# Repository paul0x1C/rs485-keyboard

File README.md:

# RS-485 Keyboard PCB
The PCB is equipped with an Arduino Nano and 24 keyboard switches and communicates via RS-485.
The keys are arranged in a 8x3 matrix. It's also possible to connect a rotary encoder and potentiometer. The keyboard is meant to control leds: press R and scroll the rotary encoder to alter the red value or H to alter hue, but I didn't code that yet.
# pictures

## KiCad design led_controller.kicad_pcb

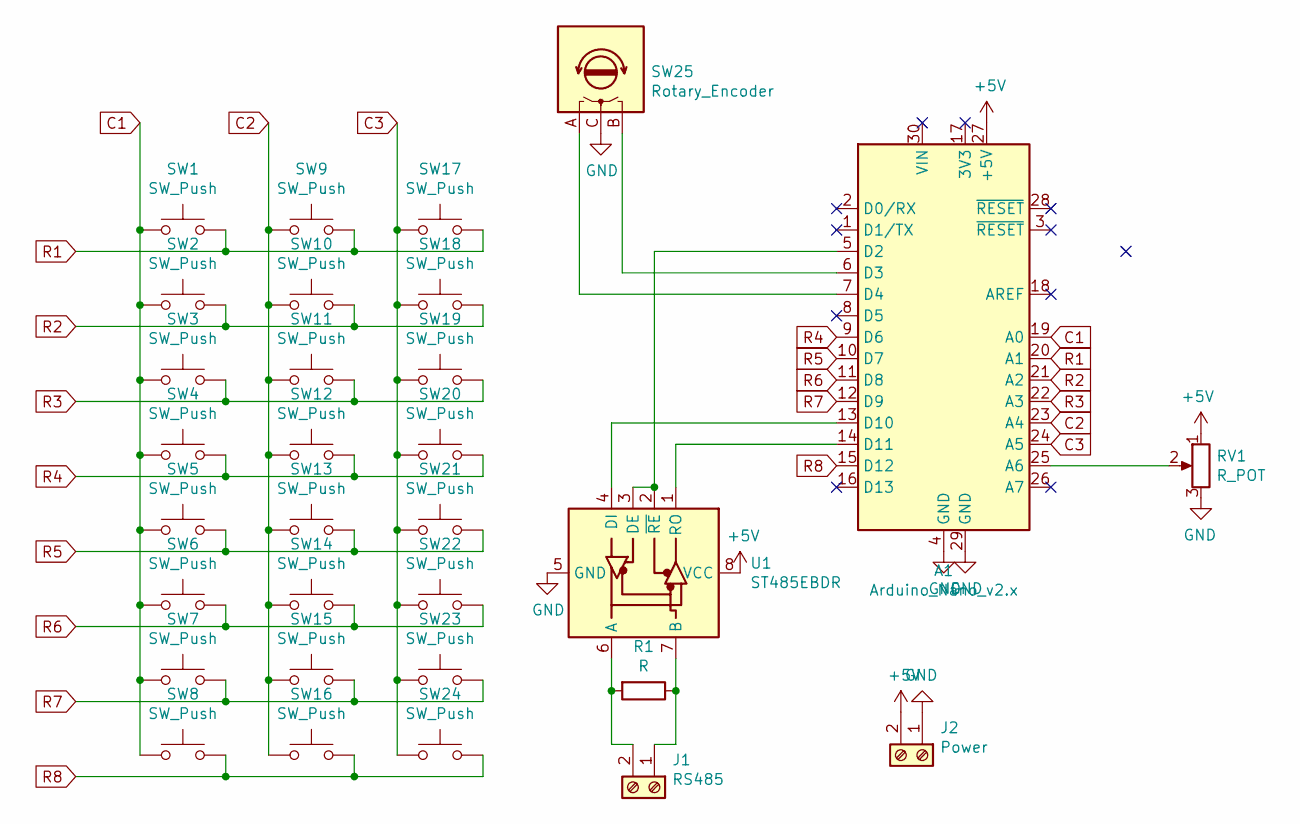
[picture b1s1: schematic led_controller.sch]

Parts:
A1: Arduino_Nano_v2.x; Arduino_Nano
J1: RS485; termina_2pin
J2: Power; termina_2pin
R1: R; R_Axial_DIN0207_L6.3mm_D2.5mm_P7.62mm_Horizontal
RV1: R_POT; PinHeader_1x03_P2.54mm_Vertical
SW1, SW2, SW3, SW4, SW5, SW6, SW7, SW8, SW9, SW10, SW11, SW12, SW13, SW14, SW15, SW16, SW17, SW18, SW19, SW20, SW21, SW22, SW23, SW24: SW_Push; SW_Cherry_MX_1.00u_PCB
SW25: Rotary_Encoder; PinHeader_1x03_P2.54mm_VerticalABC
U1: ST485EBDR; DIP-8_W7.62mm_Socket

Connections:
+5V: A1.27 (+5V), J2.2, RV1.1, U1.8 (VCC)
C1: A1.19 (A0), SW1.1, SW2.1, SW3.1, SW4.1, SW5.1, SW6.1, SW7.1, SW8.1
C2: A1.23 (A4), SW9.1, SW10.1, SW11.1, SW12.1, SW13.1, SW14.1, SW15.1, SW16.1
C3: A1.24 (A5), SW17.1, SW18.1, SW19.1, SW20.1, SW21.1, SW22.1, SW23.1, SW24.1
GND: A1.4 (GND), A1.29 (GND), J2.1, RV1.3, SW25.C, U1.5 (GND)
unnamed: A1.5 (D2), U1.2 (~RE), U1.3 (DE)
unnamed: A1.6 (D3), SW25.B
unnamed: A1.7 (D4), SW25.A
unnamed: A1.13 (D10), U1.4 (DI)
unnamed: A1.14 (D11), U1.1 (RO)
unnamed: A1.25 (A6), RV1.2
unnamed: J1.1, R1.1, U1.7 (B)
unnamed: J1.2, R1.2, U1.6 (A)
R1: A1.20 (A1), SW1.2, SW9.2, SW17.2
R2: A1.21 (A2), SW2.2, SW10.2, SW18.2
R3: A1.22 (A3), SW3.2, SW11.2, SW19.2
R4: A1.9 (D6), SW4.2, SW12.2, SW20.2
R5: A1.10 (D7), SW5.2, SW13.2, SW21.2
R6: A1.11 (D8), SW6.2, SW14.2, SW22.2
R7: A1.12 (D9), SW7.2, SW15.2, SW23.2
R8: A1.15 (D12), SW8.2, SW16.2, SW24.2

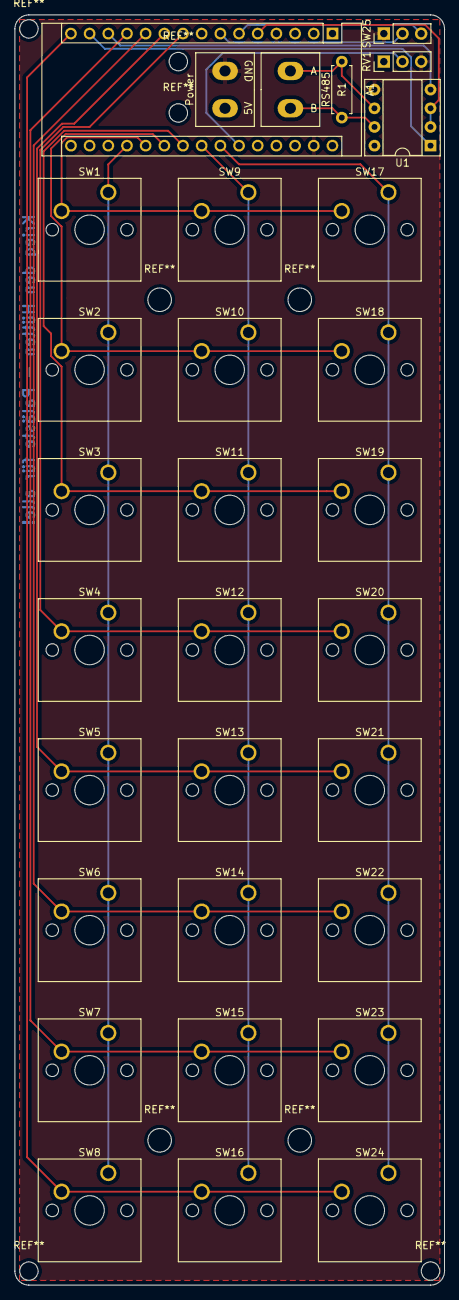
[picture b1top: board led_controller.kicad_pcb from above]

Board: 2 copper layers, 58.4 x 172.7 mm, 31 parts (0 on the bottom side), 21 nets.

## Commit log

2020-07-06 add no-connects
2020-10-13 update pcb
2020-10-13 add pictures
2020-10-13 add pictures to readme
2020-10-13 fix spelling and add info
